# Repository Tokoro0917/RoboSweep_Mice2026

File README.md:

# RoboSweep Mice2026

チーム **Mice** がロボスイープ競技に出場するためのリポジトリです。
設計データ・ソースコード・資料をここに集約し、メンバー全員で編集します。

## ディレクトリ構成

| パス | 内容 |
| --- | --- |
| `docs/` | 資料全般 |
| `docs/rules/` | 競技ルール・レギュレーションのメモ（[ルールまとめ](docs/rules/robosweep-rules.md)） |
| `docs/meetings/` | 打ち合わせの議事録（`YYYY-MM-DD_議題.md`） |
| `hardware/cad/` | 機構設計（CAD データ、図面） |
| `hardware/electrical/` | 回路図・配線図・部品表 |
| `software/firmware/` | ロボット本体のプログラム |
| `software/tools/` | 調整・解析用のツールやスクリプト |

## リポジトリの使い方

コマンドを打つ方法（ターミナル）と、画面で操作する方法（GitHub Desktop）があります。Git に慣れていない人は GitHub Desktop がおすすめです。

### 1. 最初に 1 回だけやること

1. **GitHub のアカウントを作る**：<https://github.com/> で作ります。
2. **招待を受け取る**：リポジトリの管理者に GitHub のユーザー名を伝えます。届いた招待メールの「Accept invitation」を押してください。これで編集できるようになります。
3. **道具を入れる**（どちらか片方）
   - 画面で操作する：[GitHub Desktop](https://desktop.github.com/) を入れて、GitHub のアカウントでログインする
   - コマンドで操作する：[Git](https://git-scm.com/downloads) を入れて、名前とメールアドレスを設定する
     ```bash
     git config --global user.name "あなたの名前"
     git config --global user.email "GitHub に登録したメールアドレス"
     ```
4. **クローンする**（リポジトリを自分の PC にコピーする）
   - GitHub Desktop：「File → Clone repository」で `Tokoro0917/RoboSweep_Mice2026` を選ぶ
   - コマンド：
     ```bash
     git clone https://github.com/Tokoro0917/RoboSweep_Mice2026.git
     cd RoboSweep_Mice2026
     ```
     初めて push するときは、ブラウザで GitHub にログインする画面が出ます（Windows / Mac の Git では自動で出ます）。出ないときは、GitHub のパスワードではなく [Personal access token](https://github.com/settings/tokens) を使ってください。

### 2. 作業して GitHub に上げる手順

`main` ブランチには**直接 push できません**（保護しています）。必ず「ブランチを作る → push → Pull Request」の順で上げます。

| 手順 | GitHub Desktop | コマンド |
| --- | --- | --- |
| ① `main` を最新にする | 上の「Current branch」で `main` を選び、「Fetch origin」→「Pull origin」 | `git switch main`<br>`git pull` |
| ② 作業用のブランチを作る | 「Current branch」→「New branch」。名前は [ブランチ名のルール](CONTRIBUTING.md#ブランチ名のルール) に従う | `git switch -c feature/区画走行` |
| ③ ファイルを編集する | いつもどおり CAD・エディタなどで編集・保存 | 同じ |
| ④ コミットする（変更を記録する） | 左下の「Summary」に何をしたかを書いて「Commit to ブランチ名」 | `git add 変えたファイル`<br>`git commit -m "何をしたか"` |
| ⑤ GitHub に上げる（push） | 「Push origin」（初回は「Publish branch」） | `git push -u origin ブランチ名` |
| ⑥ Pull Request を作る | 「Create Pull Request」→ ブラウザで内容を書いて作成 | GitHub のページに出る「Compare & pull request」を押す |
| ⑦ 見てもらってマージする | ほかのメンバーに確認してもらい、GitHub の PR 画面で「Merge pull request」 | 同じ |
| ⑧ 片付ける | `main` に戻って ① をやる。終わったブランチは消してよい | `git switch main`<br>`git pull` |

コミットは小さく、こまめにするのがおすすめです。PR を出したあとに直したくなったら、同じブランチでコミットして push すると、その PR に追加されます。

### 3. 困ったとき

- **push が拒否された（rejected）**：ほかの人が先に同じブランチを更新しています。pull してから、もう一度 push してください（GitHub Desktop は「Pull origin」、コマンドは `git pull`）。
- **衝突した（conflict）**：同じファイルの同じ所を 2 人が変えると起きます。テキストなら `<<<<<<<` と `>>>>>>>` の間を見て、正しいほうを残します。**CAD（.f3z）や KiCad のファイルは衝突を直せない**ので、編集する前に Issue やチャットで声をかけてください。
- **間違えて `main` で作業していた**：コミットする前なら、そのまま ② でブランチを作れば変更はそのブランチに移ります。
- 分からなくなったら、何をしたかと画面のメッセージをチャットに貼って聞いてください。

### 4. 気をつけること

- パスワードや API キーはコミットしない
- このリポジトリは公開（Public）です。公式の参考機体「ムブアイ」の資料はコミットしない（[ルールまとめ](docs/rules/robosweep-rules.md) を参照）
- ビルドで作られるファイル（`Debug/` など）や、CAD の自動バックアップは入れない（`.gitignore` で除外しています）
- やること・困っていること・決めたいことは [Issue](https://github.com/Tokoro0917/RoboSweep_Mice2026/issues) に書く

ブランチ名・コミットメッセージ・PR の書き方の決まりは [CONTRIBUTING.md](CONTRIBUTING.md) にあります。

## スケジュール

| 日付 | 内容 |
| --- | --- |
| 2026年12月末 | **練習会（当面の目標）** ※日程確認中 |
| 2027-02-20〜21 | 全日本マイクロマウス大会（ロボスイープ競技） ※予定・未確認 |

<!-- 決まったら追記してください -->

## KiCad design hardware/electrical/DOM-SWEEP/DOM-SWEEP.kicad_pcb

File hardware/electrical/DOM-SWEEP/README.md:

# DOM-SWEEP 基板

ロボットの本体基板です。**KiCad** で設計しています。

## 主な部品

| 役割 | 部品 |
| --- | --- |
| マイコン | STM32F446RET6（クロック: 10MHz セラミック発振子 CSTNE10M0G55A000R0） |
| モータドライバ | SLA7073MPRT ×2（左右のステッピングモーター用。J1 / J2） |
| 電源 | NJM7805（5V）、NJU7223F33（3.3V）、逆接続防止ダイオード 1N4007 |
| 壁センサ | 赤外 LED OS5RKA5111P ×4 ＋ フォトトランジスタ ST-1KL3A ×4 |
| その他 | ブザー UGCM1205XP、タクトスイッチ ×3、電源スイッチ、デバッグ用ヘッダ J3（2×3）、拡張ヘッダ J4（2×10） |

部品の全リストは `DOM-SWEEP.csv` を見てください。

## ファイル

| ファイル | 内容 |
| --- | --- |
| `DOM-SWEEP.kicad_pro` | プロジェクト（これを KiCad で開く） |
| `DOM-SWEEP.kicad_sch` | 回路図 |
| `DOM-SWEEP.kicad_pcb` | 基板レイアウト |
| `DOM-SWEEP.pdf` | 回路図の PDF（KiCad がなくても見られる） |
| `DOM-SWEEP.csv` | 部品表 |
| `production/` | 基板発注用のデータ（ガーバー zip、BOM、部品配置、ネットリスト） |

## 足りないもの：部品ライブラリ `new_freshman_cm`

この回路は、独自の部品ライブラリ `new_freshman_cm`（シンボルとフットプリント）を使っています。そのライブラリはこのリポジトリにまだ入っていません。

- 回路図と基板を開いて見るだけなら、ライブラリがなくても大丈夫です（使っている部品のデータはファイルの中に入っています）
- 部品を追加・変更する場合は、ライブラリを `hardware/electrical/lib/new_freshman_cm/` に置いてください（`fp-lib-table` と `sym-lib-table` はこの場所を参照しています）

## 更新するときのルール

- KiCad のファイルは 2 人が同時に編集すると衝突します。**編集する前に声をかけてください**
- 基板を発注したら、そのときのコミットにタグを付けておくと、どの版を発注したか後から分かります（例: `board-v1`）

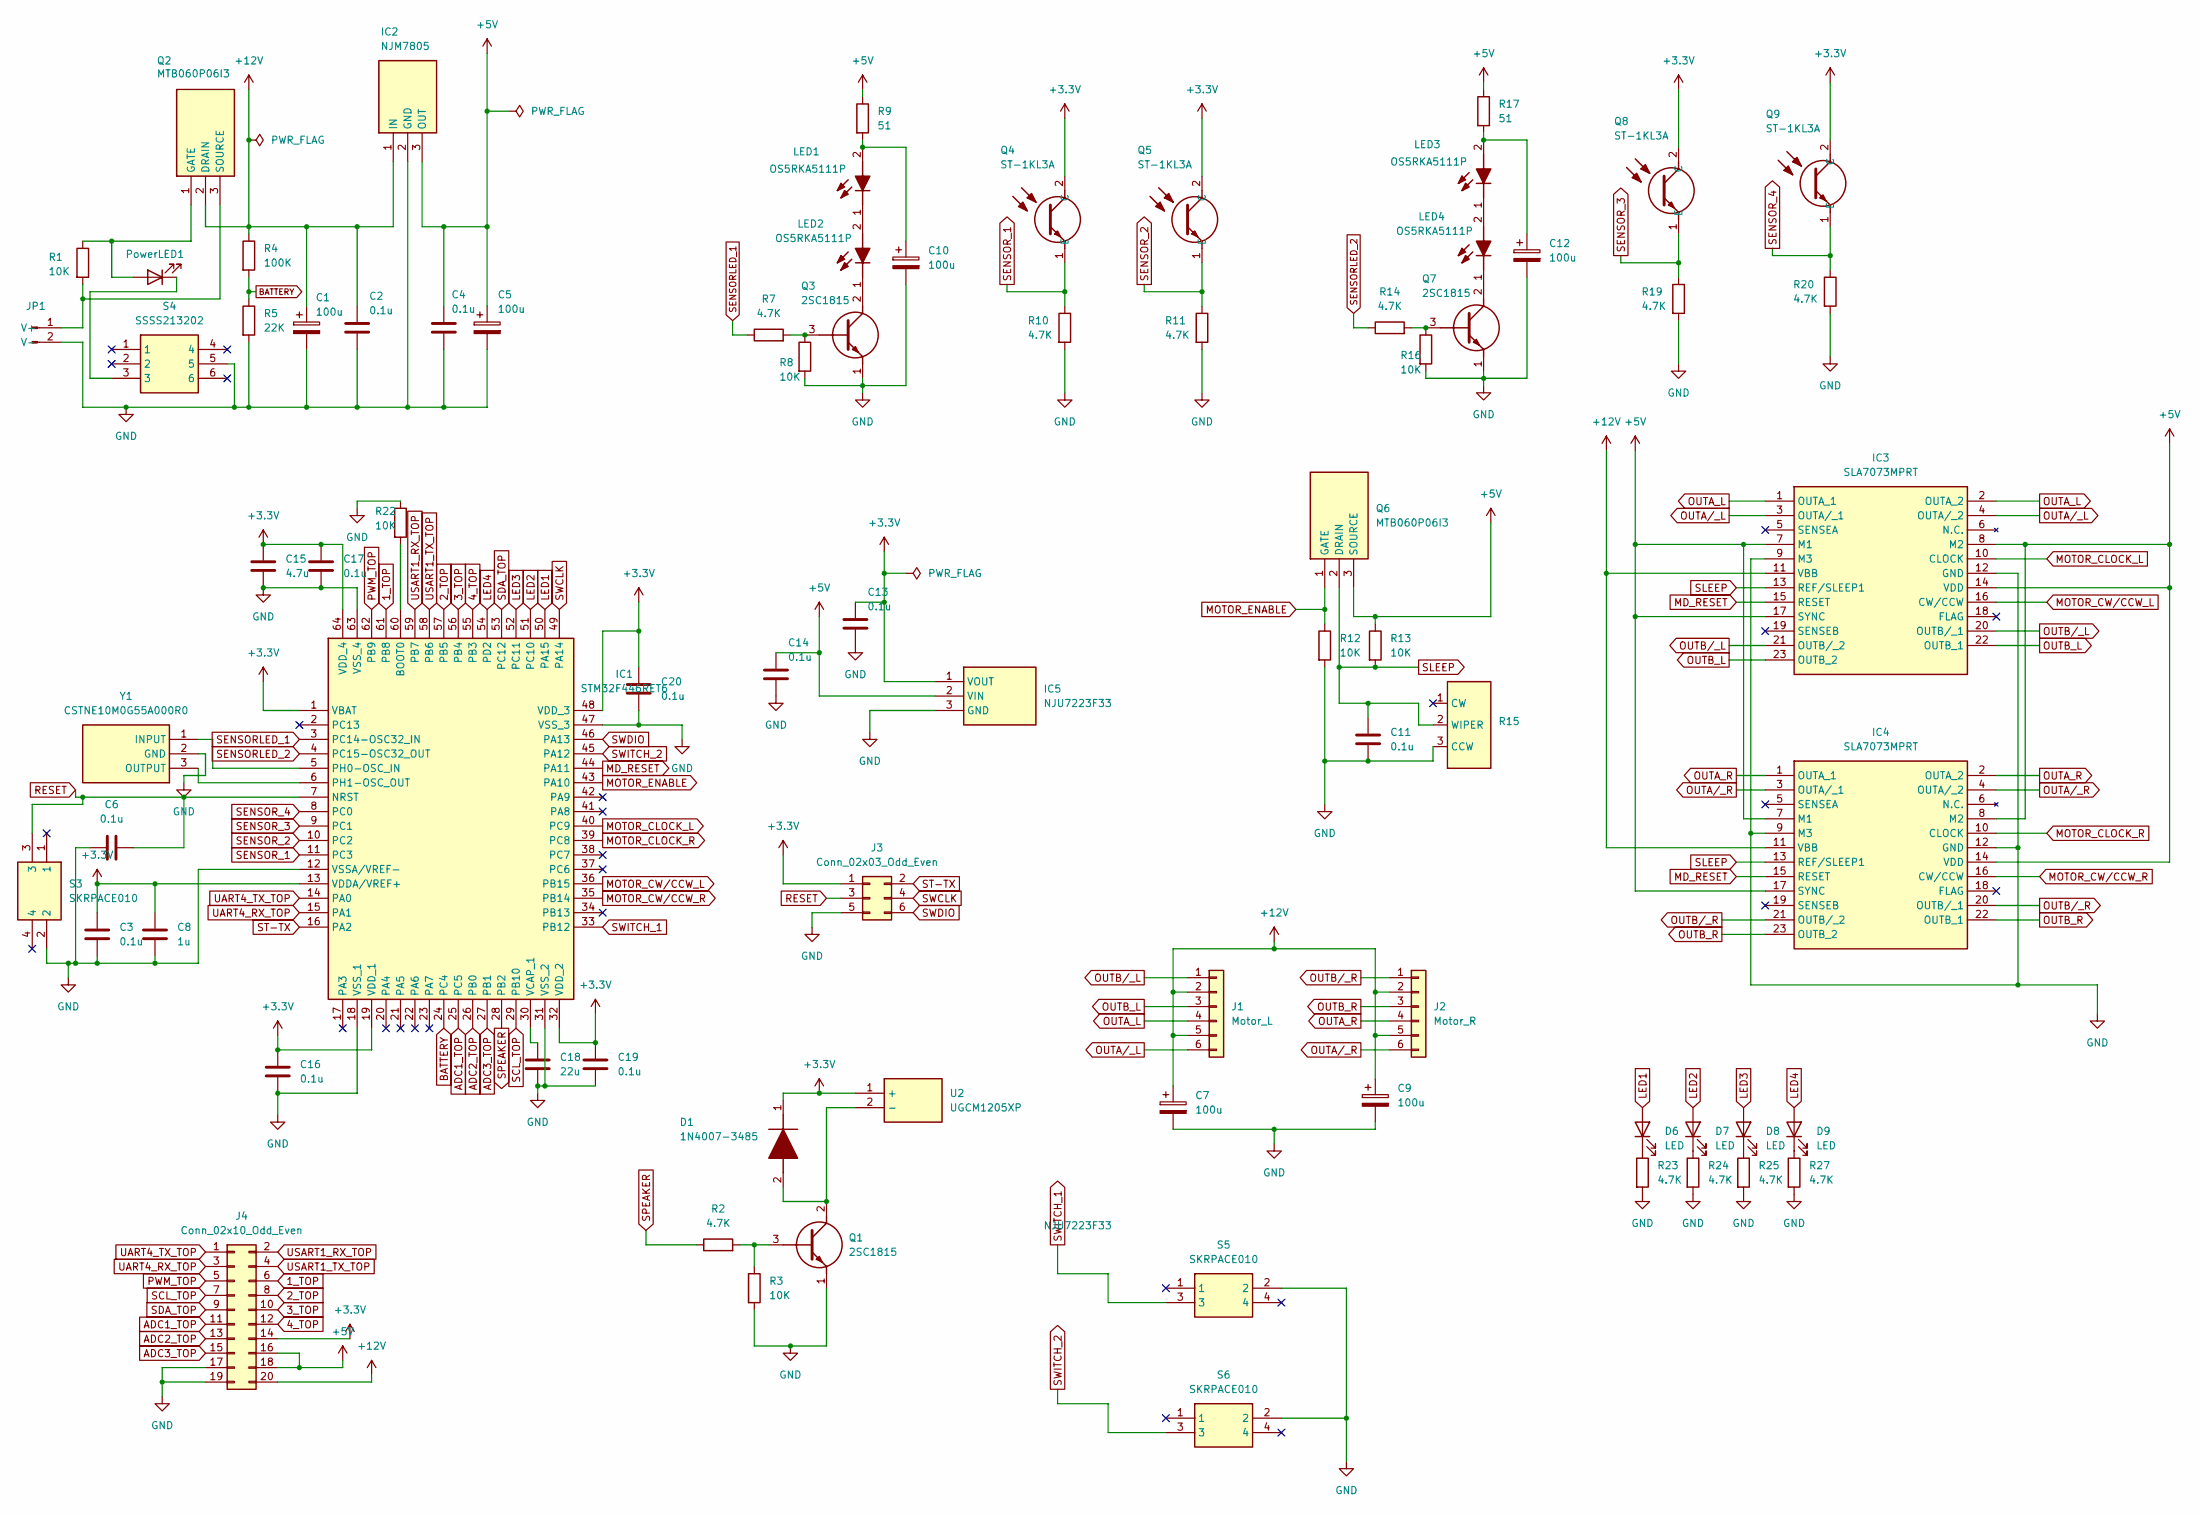
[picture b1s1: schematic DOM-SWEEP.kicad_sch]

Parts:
C1, C5, C7, C9, C10, C12: 100u; C_Radial_D5.0mm_H11.0mm_P2.00mm
C2, C3, C4, C6, C11, C13, C14, C16, C17, C19, C20: 0.1u; C_0603_1608Metric
C8: 1u; C_0603_1608Metric
C15: 4.7u; C_0603_1608Metric
C18: 22u; C_0805_2012Metric
D1: 1N4007-3485; Manufacturer_Part_Number 1N4007-3485
D6, D7, D8, D9: LED; LED_0603_1608Metric
IC1: STM32F446RET6; QFP50P1200X1200X160-64N; Manufacturer_Part_Number STM32F446RET6
IC2: NJM7805; Manufacturer_Part_Number NJM7805FA; Mouser Part Number 513-NJM7805FA
IC3, IC4: SLA7073MPRT; Manufacturer_Part_Number SLA7073MPRT
IC5: NJU7223F33; Manufacturer_Part_Number NJU7223F33; Mouser Part Number 513-NJU7223F33
J1: Motor_L; MotorPinHeader
J2: Motor_R; MotorPinHeader
J3: Conn_02x03_Odd_Even; PinHeader_2x03_P2.54mm_Vertical
J4: Conn_02x10_Odd_Even; PinHeader_2x10_P2.54mm_Vertical
JP1: BatteryTerminal
LED1, LED2, LED3, LED4: OS5RKA5111P; Manufacturer_Part_Number OS5RKA5111P
PowerLED1: LED; LED_0603_1608Metric
Q1, Q3, Q7: 2SC1815; Manufacturer_Part_Number 2SC1815; Mouser Part Number 610-2SC1815
Q2, Q6: MTB060P06I3; Manufacturer_Part_Number 2SJ681(Q); Mouser Part Number N/A
Q4, Q5, Q8, Q9: ST-1KL3A; ST1KL3A; Manufacturer_Part_Number ST-1KL3A
R1, R3, R8, R12, R13, R16, R22: 10K; R_0603_1608Metric
R2, R7, R10, R11, R14, R19, R20, R23, R24, R25, R27: 4.7K; R_0603_1608Metric
R4: 100K; R_0603_1608Metric
R5: 22K; R_0603_1608Metric
R9, R17: 51; R_0603_1608Metric
R15: Potentiometer_Bourns_3296W_Vertical
S3, S5, S6: SKRPACE010; SMT(4.2X3.2); Manufacturer_Part_Number SKRPACE010
S4: SSSS213202; Manufacturer_Part_Number SSSS213202
U2: UGCM1205XP; Manufacturer_Part_Number UGCM1205XP
Y1: CSTNE10M0G55A000R0; Manufacturer_Part_Number CSTNE10M0G55A000R0

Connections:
1_TOP: IC1.61 (PB8), J4.6
2_TOP: IC1.57 (PB5), J4.8
3_TOP: IC1.56 (PB4), J4.10
4_TOP: IC1.55 (PB3), J4.12
+3.3V: C3.1, C8.1, C13.1, C15.1, C16.1, C17.1, C19.1, C20.1, D1.1 (K), IC1.1 (VBAT), IC1.13 (VDDA/VREF+), IC1.19 (VDD_1), IC1.32 (VDD_2), IC1.48 (VDD_3), IC1.64 (VDD_4), IC5.1 (VOUT), J3.1, J4.14, Q4.2 (C), Q5.2 (C), Q8.2 (C), Q9.2 (C), U2.1 (+)
+5V: C4.1, C5.1, C14.1, IC2.3 (OUT), IC3.7 (M1), IC3.8 (M2), IC3.14 (VDD), IC3.17 (SYNC), IC4.7 (M1), IC4.8 (M2), IC4.14 (VDD), IC4.17 (SYNC), IC5.2 (VIN), J4.16, J4.18, Q6.3 (SOURCE), R9.1, R13.1, R17.1
+12V: C1.1, C2.1, C7.1, C9.1, IC2.1 (IN), IC3.11 (VBB), IC4.11 (VBB), J1.2, J1.5, J2.2, J2.5, J4.20, Q2.2 (DRAIN), R4.1
ADC1_TOP: IC1.25 (PC5), J4.11
ADC2_TOP: IC1.26 (PB0), J4.13
ADC3_TOP: IC1.27 (PB1), J4.15
BATTERY: IC1.24 (PC4), R4.2, R5.1
GND: C1.2, C2.2, C3.2, C4.2, C5.2, C6.1, C7.2, C8.2, C9.2, C10.2, C11.2, C12.2, C13.2, C14.2, C15.2, C16.2, C17.2, C18.2, C19.2, C20.2, IC1.12 (VSSA/VREF-), IC1.18 (VSS_1), IC1.31 (VSS_2), IC1.47 (VSS_3), IC1.63 (VSS_4), IC2.2 (GND), IC3.9 (M3), IC3.12 (GND), IC4.9 (M3), IC4.12 (GND), IC5.3 (GND), J3.5, J4.17, J4.19, JP1.2 (V-), Q1.1 (E), Q3.1 (E), Q7.1 (E), R3.2, R5.2, R8.2, R10.2, R11.2, R12.2, R15.3 (CCW), R16.2, R19.2, R20.2, R22.1, R23.2, R24.2, R25.2, R27.2, S3.2, S4.5, S5.2, S6.2, Y1.2 (GND)
LED1: D6.2 (A), IC1.50 (PA15)
LED2: D7.2 (A), IC1.51 (PC10)
LED3: D8.2 (A), IC1.52 (PC11)
LED4: D9.2 (A), IC1.54 (PD2)
MD_RESET: IC1.44 (PA11), IC3.15 (RESET), IC4.15 (RESET)
MOTOR_CLOCK_L: IC1.40 (PC9), IC3.10 (CLOCK)
MOTOR_CLOCK_R: IC1.39 (PC8), IC4.10 (CLOCK)
MOTOR_CW/CCW_L: IC1.36 (PB15), IC3.16 (CW/CCW)
MOTOR_CW/CCW_R: IC1.35 (PB14), IC4.16 (CW/CCW)
MOTOR_ENABLE: IC1.43 (PA10), Q6.1 (GATE), R12.1
unnamed: D1.2 (A), Q1.2 (C), U2.2 (-)
unnamed: D6.1 (K), R23.1
unnamed: D7.1 (K), R24.1
unnamed: D8.1 (K), R25.1
unnamed: D9.1 (K), R27.1
unnamed: IC1.60 (BOOT0), R22.2
unnamed: IC1.5 (PH0-OSC_IN), Y1.1 (INPUT)
unnamed: IC1.6 (PH1-OSC_OUT), Y1.3 (OUTPUT)
unnamed: C18.1, IC1.30 (VCAP_1)
unnamed: JP1.1 (V+), Q2.3 (SOURCE), R1.2
unnamed: C10.1, LED1.2 (A), R9.2
unnamed: LED1.1 (K), LED2.2 (A)
unnamed: LED2.1 (K), Q3.2 (C)
unnamed: C12.1, LED3.2 (A), R17.2
unnamed: LED3.1 (K), LED4.2 (A)
unnamed: LED4.1 (K), Q7.2 (C)
unnamed: PowerLED1.2 (A), Q2.1 (GATE), R1.1
unnamed: PowerLED1.1 (K), S4.3
unnamed: Q1.3 (B), R2.2, R3.1
unnamed: Q3.3 (B), R7.2, R8.1
unnamed: Q7.3 (B), R14.2, R16.1
OUTA_L: IC3.1 (OUTA_1), IC3.2 (OUTA_2), J1.4
OUTA_R: IC4.1 (OUTA_1), IC4.2 (OUTA_2), J2.4
OUTA/_L: IC3.3 (OUTA/_1), IC3.4 (OUTA/_2), J1.6
OUTA/_R: IC4.3 (OUTA/_1), IC4.4 (OUTA/_2), J2.6
OUTB_L: IC3.22 (OUTB_1), IC3.23 (OUTB_2), J1.3
OUTB_R: IC4.22 (OUTB_1), IC4.23 (OUTB_2), J2.3
OUTB/_L: IC3.20 (OUTB/_1), IC3.21 (OUTB/_2), J1.1
OUTB/_R: IC4.20 (OUTB/_1), IC4.21 (OUTB/_2), J2.1
PWM_TOP: IC1.62 (PB9), J4.5
RESET: C6.2, IC1.7 (NRST), J3.3, S3.3
SCL_TOP: IC1.29 (PB10), J4.7
SDA_TOP: IC1.53 (PC12), J4.9
SENSORLED_1: IC1.3 (PC14-OSC32_IN), R7.1
SENSORLED_2: IC1.4 (PC15-OSC32_OUT), R14.1
SENSOR_1: IC1.11 (PC3), Q4.1 (E), R10.1
SENSOR_2: IC1.10 (PC2), Q5.1 (E), R11.1
SENSOR_3: IC1.9 (PC1), Q8.1 (E), R19.1
SENSOR_4: IC1.8 (PC0), Q9.1 (E), R20.1
SLEEP: C11.1, IC3.13 (REF/SLEEP1), IC4.13 (REF/SLEEP1), Q6.2 (DRAIN), R13.2, R15.2 (WIPER)
SPEAKER: IC1.28 (PB2), R2.1
ST-TX: IC1.16 (PA2), J3.2
SWCLK: IC1.49 (PA14), J3.4
SWDIO: IC1.46 (PA13), J3.6
SWITCH_1: IC1.33 (PB12), S5.3
SWITCH_2: IC1.45 (PA12), S6.3
UART4_RX_TOP: IC1.15 (PA1), J4.3
UART4_TX_TOP: IC1.14 (PA0), J4.1
USART1_RX_TOP: IC1.59 (PB7), J4.2
USART1_TX_TOP: IC1.58 (PB6), J4.4

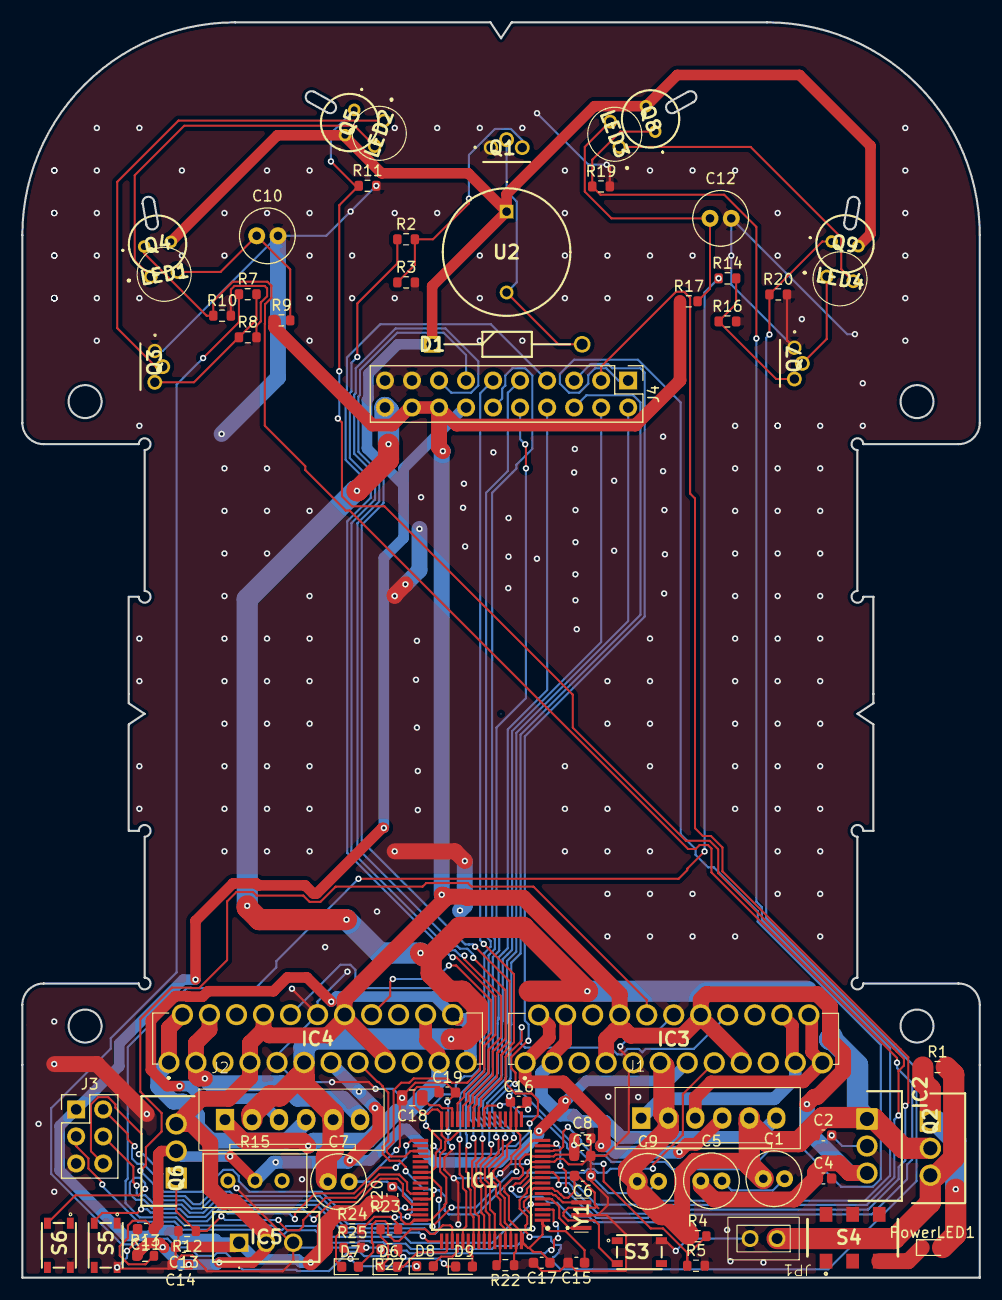
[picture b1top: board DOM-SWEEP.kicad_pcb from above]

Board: 2 copper layers, 90.0 x 118.0 mm, 78 parts (0 on the bottom side), 72 nets.

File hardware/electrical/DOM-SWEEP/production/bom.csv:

Designator,Footprint,Quantity,Value,LCSC Part #
"C1, C10, C12, C5, C7, C9",C_Radial_D5.0mm_H11.0mm_P2.00mm,6,100u,
"C11, C13, C14, C16, C17, C19, C2, C20, C3, C4, C6",0603,11,0.1u,
C15,0603,1,4.7u,
C18,0805,1,22u,
C8,0603,1,1u,
D1,1N4007-3485,1,1N4007-3485,
"D6, D7, D8, D9, POWERLED1",0603,5,LED,
IC1,QFP50P1200X1200X160-64N,1,STM32F446RET6,
IC2,NJM7805,1,NJM7805,
"IC3, IC4",SLA7073MPRT,2,SLA7073MPRT,
IC5,NJU7223F33,1,NJU7223F33,
J1,MotorPinHeader,1,Motor_L,
J2,MotorPinHeader,1,Motor_R,
J3,PinHeader_2x03_P2.54mm_Vertical,1,Conn_02x03_Odd_Even,
J4,PinHeader_2x10_P2.54mm_Vertical,1,Conn_02x10_Odd_Even,
JP1,BatteryTerminal,1,~,
"LED1, LED2, LED3, LED4",OS5RKA5111P,4,OS5RKA5111P,
"Q1, Q3, Q7",2SC1815,3,2SC1815,
"Q2, Q6",MTB060P06I3,2,MTB060P06I3,
"Q4, Q5, Q8, Q9",ST1KL3A,4,ST-1KL3A,
"R1, R12, R13, R16, R22, R3, R8",0603,7,10K,
"R10, R11, R14, R19, R2, R20, R23, R24, R25, R27, R7",0603,11,4.7K,
R15,Potentiometer_Bourns_3296W_Vertical,1,~,
"R17, R9",0603,2,51,
R4,0603,1,100K,
R5,0603,1,22K,
"S3, S5, S6",SMT(4.2X3.2),3,SKRPACE010,
S4,SSSS213202,1,SSSS213202,
U2,UGCM1205XP,1,UGCM1205XP,
Y1,CSTNE10M0G55A000R0,1,CSTNE10M0G55A000R0,

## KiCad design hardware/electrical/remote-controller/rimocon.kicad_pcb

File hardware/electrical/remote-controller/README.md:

# リモコン基板（rimocon）

機体を手で動かして試すためのリモコンの基板です。**KiCad** で設計しています。プログラムは [`software/firmware/remote_controller/`](../../../software/firmware/remote_controller/) にあります。

## 主な部品

| 部品 | 内容 |
| --- | --- |
| U1 | Seeed Studio XIAO ESP32C3（ESP-NOW で機体に送信） |
| DS1 | AQM0802A（8 文字 × 2 行の I2C 液晶） |
| SW1〜SW8 | タクトスイッチ 8 個（A / B / X / Y / L / R / F / Back） |
| D1, D2 | LED |

## ファイル

| ファイル | 内容 |
| --- | --- |
| `rimocon.kicad_pro` | プロジェクト（これを KiCad で開く） |
| `rimocon.kicad_sch` / `rimocon.kicad_pcb` | 回路図 / 基板 |
| `production/` | 基板発注用のデータ |
| `lib/xiao_esp32c3/` | XIAO ESP32C3 のシンボルとフットプリント（GPL-3.0、作者のライセンスファイル付き） |

## 足りないもの：AQM0802A のライブラリ

AQM0802A のシンボルとフットプリントは SamacSys（Component Search Engine）のものです。このライブラリは規約で配布が禁止されているので、リポジトリには入れていません。部品を変更するときは、各自で [Component Search Engine](https://componentsearchengine.com/) から「AQM0802A」をダウンロードしてください。回路図と基板を見るだけなら、ダウンロードしなくても大丈夫です。

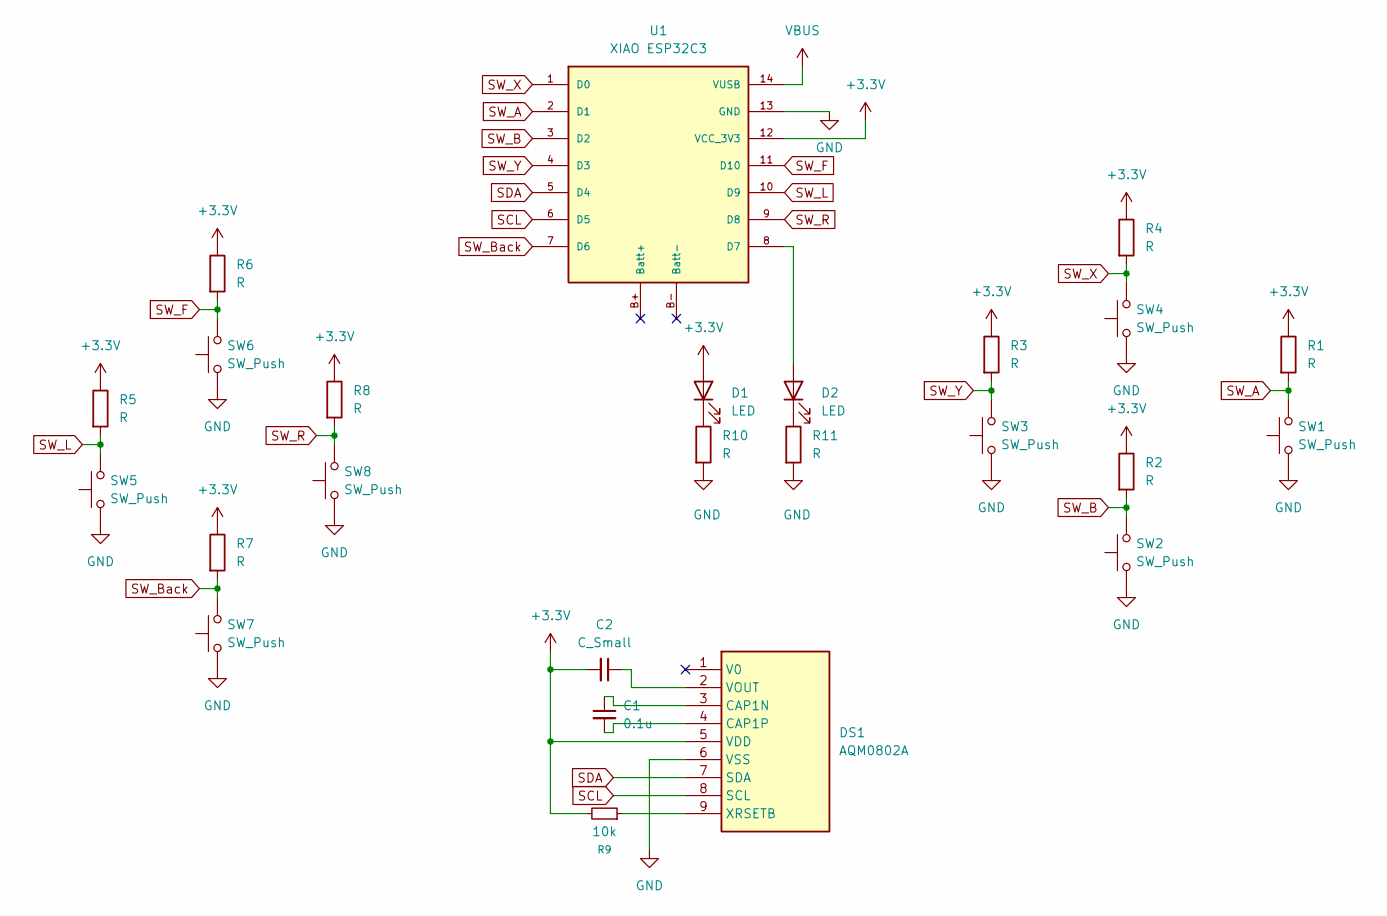
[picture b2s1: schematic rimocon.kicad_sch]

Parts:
C1: 0.1u; C_0603_1608Metric
C2: C_Small; C_0603_1608Metric
D1, D2: LED; LED_D3.0mm
DS1: AQM0802A; Manufacturer_Part_Number AQM0802A
R1, R2, R3, R4, R5, R6, R7, R8, R10, R11: R; R_0603_1608Metric
R9: 10k; R_0603_1608Metric
SW1, SW2, SW3, SW4, SW5, SW6, SW7, SW8: SW_Push; SW_PUSH_6mm
U1: XIAO ESP32C3; xiao_esp32c3

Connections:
+3.3V: C2.2, D1.2 (A), DS1.5 (VDD), R1.1, R2.1, R3.1, R4.1, R5.1, R6.1, R7.1, R8.1, R9.2, U1.12 (VCC_3V3)
GND: DS1.6 (VSS), R10.2, R11.2, SW1.1, SW2.1, SW3.1, SW4.1, SW5.1, SW6.1, SW7.1, SW8.1, U1.13 (GND)
unnamed: D1.1 (K), R10.1
unnamed: D2.2 (A), U1.8 (D7)
unnamed: D2.1 (K), R11.1
unnamed: C1.1, DS1.3 (CAP1N)
unnamed: C1.2, DS1.4 (CAP1P)
unnamed: C2.1, DS1.2 (VOUT)
unnamed: DS1.9 (XRSETB), R9.1
SCL: DS1.8 (SCL), U1.6 (D5)
SDA: DS1.7 (SDA), U1.5 (D4)
SW_A: R1.2, SW1.2, U1.2 (D1)
SW_B: R2.2, SW2.2, U1.3 (D2)
SW_Back: R7.2, SW7.2, U1.7 (D6)
SW_F: R6.2, SW6.2, U1.11 (D10)
SW_L: R5.2, SW5.2, U1.10 (D9)
SW_R: R8.2, SW8.2, U1.9 (D8)
SW_X: R4.2, SW4.2, U1.1 (D0)
SW_Y: R3.2, SW3.2, U1.4 (D3)
VBUS: U1.14 (VUSB)

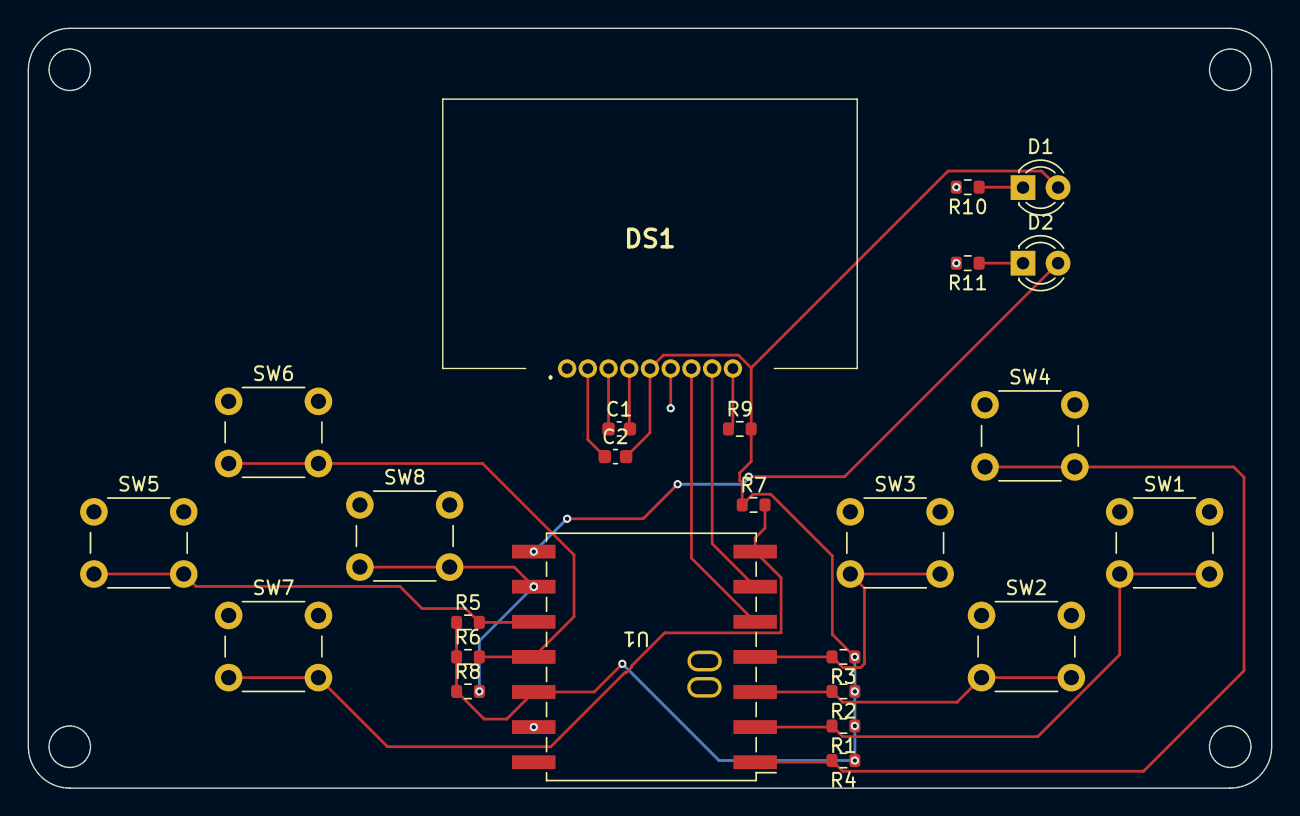
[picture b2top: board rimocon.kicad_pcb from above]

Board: 2 copper layers, 90.0 x 55.0 mm, 25 parts (0 on the bottom side), 19 nets.

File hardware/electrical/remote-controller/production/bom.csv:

Designator,Footprint,Quantity,Value,LCSC Part #
C1,0603,1,0.1u,
C2,0603,1,C_Small,
"D1, D2",LED_D3.0mm,2,LED,
DS1,AQM0802A,1,AQM0802A,
"R1, R10, R11, R2, R3, R4, R5, R6, R7, R8",0603,10,R,
R9,0603,1,10k,
"SW1, SW2, SW3, SW4, SW5, SW6, SW7, SW8",SW_PUSH_6mm,8,SW_Push,
U1,xiao_esp32c3,1,XIAO ESP32C3,

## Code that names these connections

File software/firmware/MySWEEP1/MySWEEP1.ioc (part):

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Mcu.Name=STM32F446R(C-E)Tx
Mcu.Package=LQFP64
Mcu.UserName=STM32F446RETx
PA0-WKUP.Mode=Asynchronous
PA0-WKUP.Signal=UART4_TX
PA1.Mode=Asynchronous
PA1.Signal=UART4_RX
PA10.GPIOParameters=GPIO_Label
PA10.GPIO_Label=MOTOR_ENABLE
PA10.Signal=GPIO_Output
PA11.GPIOParameters=GPIO_Label
PA11.GPIO_Label=MD_RESET
PA11.Signal=GPIO_Output
PA15.GPIOParameters=GPIO_Label
PA15.GPIO_Label=LED_1
PA15.Signal=GPIO_Output
PA2.Mode=Asynchronous
PA2.Signal=USART2_TX
PA3.Mode=Asynchronous
PA3.Signal=USART2_RX
PB14.GPIOParameters=GPIO_Label
PB14.GPIO_Label=MOTOR_CW/CCW_R
PB14.Signal=GPIO_Output
PB15.GPIOParameters=GPIO_Label
PB15.GPIO_Label=MOTOR_CW/CCW_L
PB15.Signal=GPIO_Output
PB6.Mode=Asynchronous
PB6.Signal=USART1_TX
PB7.Mode=Asynchronous
PB7.Signal=USART1_RX
PB8.GPIOParameters=GPIO_Label
PB8.GPIO_Label=LED_T1
PB8.Signal=GPIO_Output
PB9.Signal=S_TIM4_CH4
PC0.GPIOParameters=GPIO_Label
PC0.GPIO_Label=SENSOR_4
PC0.Signal=ADCx_IN10
PC1.GPIOParameters=GPIO_Label
PC1.GPIO_Label=SENSOR_3
PC1.Signal=ADCx_IN11
PC10.GPIOParameters=GPIO_Label
PC10.GPIO_Label=LED_2
PC10.Signal=GPIO_Output
PC14-OSC32_IN.GPIOParameters=GPIO_Label
PC14-OSC32_IN.GPIO_Label=SENSORLED_1
PC14-OSC32_IN.Signal=GPIO_Output
PC15-OSC32_OUT.GPIOParameters=GPIO_Label
PC15-OSC32_OUT.GPIO_Label=SENSORLED_2
PC15-OSC32_OUT.Signal=GPIO_Output
PC2.GPIOParameters=GPIO_Label
PC2.GPIO_Label=SENSOR_2
PC2.Signal=ADCx_IN12
PC3.GPIOParameters=GPIO_Label
PC3.GPIO_Label=SENSOR_1
PC3.Signal=ADCx_IN13
PC5.Signal=ADCx_IN15
PC8.GPIOParameters=GPIO_Label
PC8.GPIO_Label=MOTOR_CLOCK_R
PC8.Signal=S_TIM3_CH3
PC9.GPIOParameters=GPIO_Label
PC9.GPIO_Label=MOTOR_CLOCK_L
PC9.Signal=S_TIM8_CH4
PH0-OSC_IN.Mode=HSE-External-Oscillator
PH0-OSC_IN.Signal=RCC_OSC_IN
PH1-OSC_OUT.Mode=HSE-External-Oscillator
PH1-OSC_OUT.Signal=RCC_OSC_OUT
RCC.SYSCLKFreq_VALUE=180000000
RCC.SYSCLKSource=RCC_SYSCLKSOURCE_PLLCLK
board=custom

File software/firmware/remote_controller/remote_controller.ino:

#include <WiFi.h>
#include <esp_now.h>
#include <Wire.h>

// ==========================================
// 1. LCD (AQM0802A) 制御用の直叩き関数
// ==========================================
const int I2C_ADDR = 0x3E;

void lcd_cmd(uint8_t cmd) {
  Wire.beginTransmission(I2C_ADDR);
  Wire.write(0x00);
  Wire.write(cmd);
  Wire.endTransmission();
  delay(1);
}

void lcd_data(uint8_t data) {
  Wire.beginTransmission(I2C_ADDR);
  Wire.write(0x40);
  Wire.write(data);
  Wire.endTransmission();
  delay(1);
}

void lcd_init() {
  delay(100);
  lcd_cmd(0x38); // Function set: 8-bit, 2-line, normal font, IS=0
  lcd_cmd(0x39); // Function set: 8-bit, 2-line, normal font, IS=1
  lcd_cmd(0x14); // Internal OSC frequency
  lcd_cmd(0x73); // Contrast set (見えにくい場合は 0x70〜0x7F で調整)
  lcd_cmd(0x56); // Power/ICON/Contrast: Booster ON (3.3V用)
  lcd_cmd(0x6C); // Follower control
  delay(200);    // 電圧昇圧待ち
  lcd_cmd(0x38); // Function set: IS=0
  lcd_cmd(0x0C); // Display ON, cursor OFF
  lcd_cmd(0x01); // Clear display
  delay(2);
}

void lcd_print(const char* str) {
  while (*str) {
    lcd_data(*str++);
  }
}

// ==========================================
// 2. ESP-NOW 通信設定
// ==========================================

// ★ここに機体側のMACアドレスを入力してください (例: 0x34, 0x85, 0x18, ...)
uint8_t receiverAddress[] = {0x90, 0x70, 0x69, 0x12, 0xBF, 0x90};

typedef struct struct_message {
  bool btnA;
  bool btnB;
  bool btnX;
  bool btnY;
  bool btnL;
  bool btnR;
  bool btnF;
  bool btnBack;
} struct_message;

struct_message myData;

// ピン割り当て
const int PIN_SW_X = D0;
const int PIN_SW_A = D1;
const int PIN_SW_B = D2;
const int PIN_SW_Y = D3;
// SDA=D4, SCL=D5 はWire.beginで使用
const int PIN_SW_BACK = D6;
const int PIN_SW_R = D8;
const int PIN_SW_L = D9;
const int PIN_SW_F = D10;

String lastDisplay = ""; // 画面のちらつき防止用

void OnDataSent(const uint8_t *mac_addr, esp_now_send_status_t status) {
  // 送信完了時のコールバック（必要に応じて処理追加）
}

// ==========================================
// 3. セットアップ
// ==========================================
void setup() {
  Serial.begin(115200);

  // LCDの初期化
  Wire.begin(D4, D5);
  lcd_init();

  lcd_cmd(0x80); // 1行目の先頭
  lcd_print("ESP-NOW ");
  lcd_cmd(0xC0); // 2行目の先頭
  lcd_print("Ready...");
  delay(1500);
  lcd_cmd(0x01); // 画面クリア
  delay(2);

  // ボタンピンの設定
  pinMode(PIN_SW_A, INPUT);
  pinMode(PIN_SW_B, INPUT);
  pinMode(PIN_SW_X, INPUT);
  pinMode(PIN_SW_Y, INPUT);
  pinMode(PIN_SW_L, INPUT);
  pinMode(PIN_SW_R, INPUT);
  pinMode(PIN_SW_F, INPUT);
  pinMode(PIN_SW_BACK, INPUT);

  // ESP-NOWの初期化
  WiFi.mode(WIFI_STA);
  delay(100);
  // このリモコンの MAC アドレス。robot_receiver.ino の REMOTE_MAC に書く
  Serial.print("Remote MAC address: ");
  Serial.println(WiFi.macAddress());
  if (esp_now_init() != ESP_OK) {
    lcd_cmd(0x80); lcd_print("ERR:WIFI");
    return;
  }
  esp_now_register_send_cb((esp_now_send_cb_t)OnDataSent);

  // ピア(機体側)の登録
  esp_now_peer_info_t peerInfo = {};
  memcpy(peerInfo.peer_addr, receiverAddress, 6);
  peerInfo.channel = 1;  
  peerInfo.encrypt = false;
  if (esp_now_add_peer(&peerInfo) != ESP_OK){
    lcd_cmd(0x80); lcd_print("ERR:PEER");
    return;
  }
}

// ==========================================
// 4. メインループ
// ==========================================
void loop() {
  // ボタン状態取得 (押されるとLOWなので反転)
  myData.btnA    = !digitalRead(PIN_SW_A);
  myData.btnB    = !digitalRead(PIN_SW_B);
  myData.btnX    = !digitalRead(PIN_SW_X);
  myData.btnY    = !digitalRead(PIN_SW_Y);
  myData.btnL    = !digitalRead(PIN_SW_L);
  myData.btnR    = !digitalRead(PIN_SW_R);
  myData.btnF    = !digitalRead(PIN_SW_F);
  myData.btnBack = !digitalRead(PIN_SW_BACK);

  // LCD表示文字列の生成 (8文字制限)
  String currentDisplay = "IDLE    ";
  
  if (myData.btnF) {
    currentDisplay = "CMD: F  ";
  } else if (myData.btnBack) {
    currentDisplay = "CMD: BAC"; 
  } else if (myData.btnL) {
    currentDisplay = "CMD: L  ";
  } else if (myData.btnR) {
    currentDisplay = "CMD: R  ";
  } else if (myData.btnX) {
    currentDisplay = "CMD: X  ";
  } else if (myData.btnY) {
    currentDisplay = "CMD: Y  ";
  } else if (myData.btnA) {
    currentDisplay = "CMD: A  ";
  } else if (myData.btnB) {
    currentDisplay = "CMD: B  ";
  }

  // 状態が変わった時だけLCDを更新
  if (currentDisplay != lastDisplay) {
    lcd_cmd(0x80); // 1行目
    lcd_print("Status: ");
    
    lcd_cmd(0xC0); // 2行目
    lcd_print(currentDisplay.c_str());
    
    lastDisplay = currentDisplay;
  }

  // データ送信
  esp_now_send(receiverAddress, (uint8_t *) &myData, sizeof(myData));
  
  delay(50); // 送信間隔 (50ms)
}
